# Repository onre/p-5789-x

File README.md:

# p-5789-x

Shield: [![CC BY-SA 4.0][cc-by-sa-shield]][cc-by-sa]

This work is licensed under a
[Creative Commons Attribution-ShareAlike 4.0 International License][cc-by-sa].

[![CC BY-SA 4.0][cc-by-sa-image]][cc-by-sa]

[cc-by-sa]: http://creativecommons.org/licenses/by-sa/4.0/
[cc-by-sa-image]: https://licensebuttons.net/l/by-sa/4.0/88x31.png
[cc-by-sa-shield]: https://img.shields.io/badge/License-CC%20BY--SA%204.0-lightgrey.svg

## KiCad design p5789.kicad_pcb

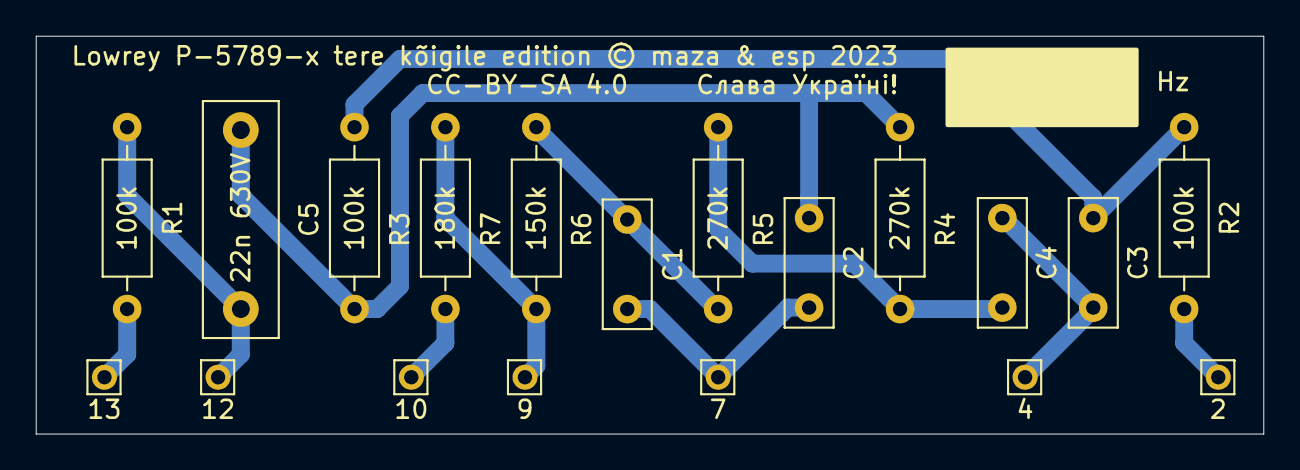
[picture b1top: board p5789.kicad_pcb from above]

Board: 2 copper layers, 68.6 x 22.2 mm, 19 parts (0 on the bottom side), 11 nets.

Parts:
2, 4, 7, 9, 10, 12, 13: Pin_D0.7mm_L6.5mm_W1.8mm_FlatFork
C1, C2, C3, C4: variable; C_Rect_L7.0mm_W2.5mm_P5.00mm
C5: 22 nF 400 V; C_Rect_L13.0mm_W4.0mm_P10.00mm_FKS3_FKP3_MKS4
R1, R2, R3: 100 k; R_Axial_DIN0207_L6.3mm_D2.5mm_P10.16mm_Horizontal
R4, R5: 270 k; R_Axial_DIN0207_L6.3mm_D2.5mm_P10.16mm_Horizontal
R6: 150 k; R_Axial_DIN0207_L6.3mm_D2.5mm_P10.16mm_Horizontal
R7: 180 k; R_Axial_DIN0207_L6.3mm_D2.5mm_P10.16mm_Horizontal

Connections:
2_output: 2.2, R2.2
4_gnd: 4.4, C3.2, C4.1
7_tuning: 7.7, C1.1, C2.2
9_grid: 9.9, R6.1, R7.2
10_input: 10.10, R7.1
12_plate: 12.12, C5.1, R1.1
13_b+: 13.13, R1.2
unnamed: C1.2, R5.1, R6.2
unnamed: C2.1, C5.2, R3.1, R4.1
unnamed: C3.1, R2.1, R3.2
unnamed: C4.2, R4.2, R5.2

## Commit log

2023-06-21 first attempt at this
2023-06-21 add license

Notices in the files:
p5789.kicad_pcb:
Lowrey P-5789-x tere kõigile edition © maza & esp 2023
CC-BY-SA 4.0 Слава Україні!
